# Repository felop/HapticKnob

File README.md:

# Haptic Knob

Développement d’un dispositif à retour haptique contrôlant l’éclairage d’une maquette. Modélisation de textures ressenties sous les doigts, à partir de fonctions simulant des forces de frottement, ressorts internes et effets de seuil, ajustables dynamiquement pour créer crans, irrégularités ou zones fluides. Système conçu autour d’un moteur BLDC et d’un encodeur magnétique (MT6701), piloté par un esp32.

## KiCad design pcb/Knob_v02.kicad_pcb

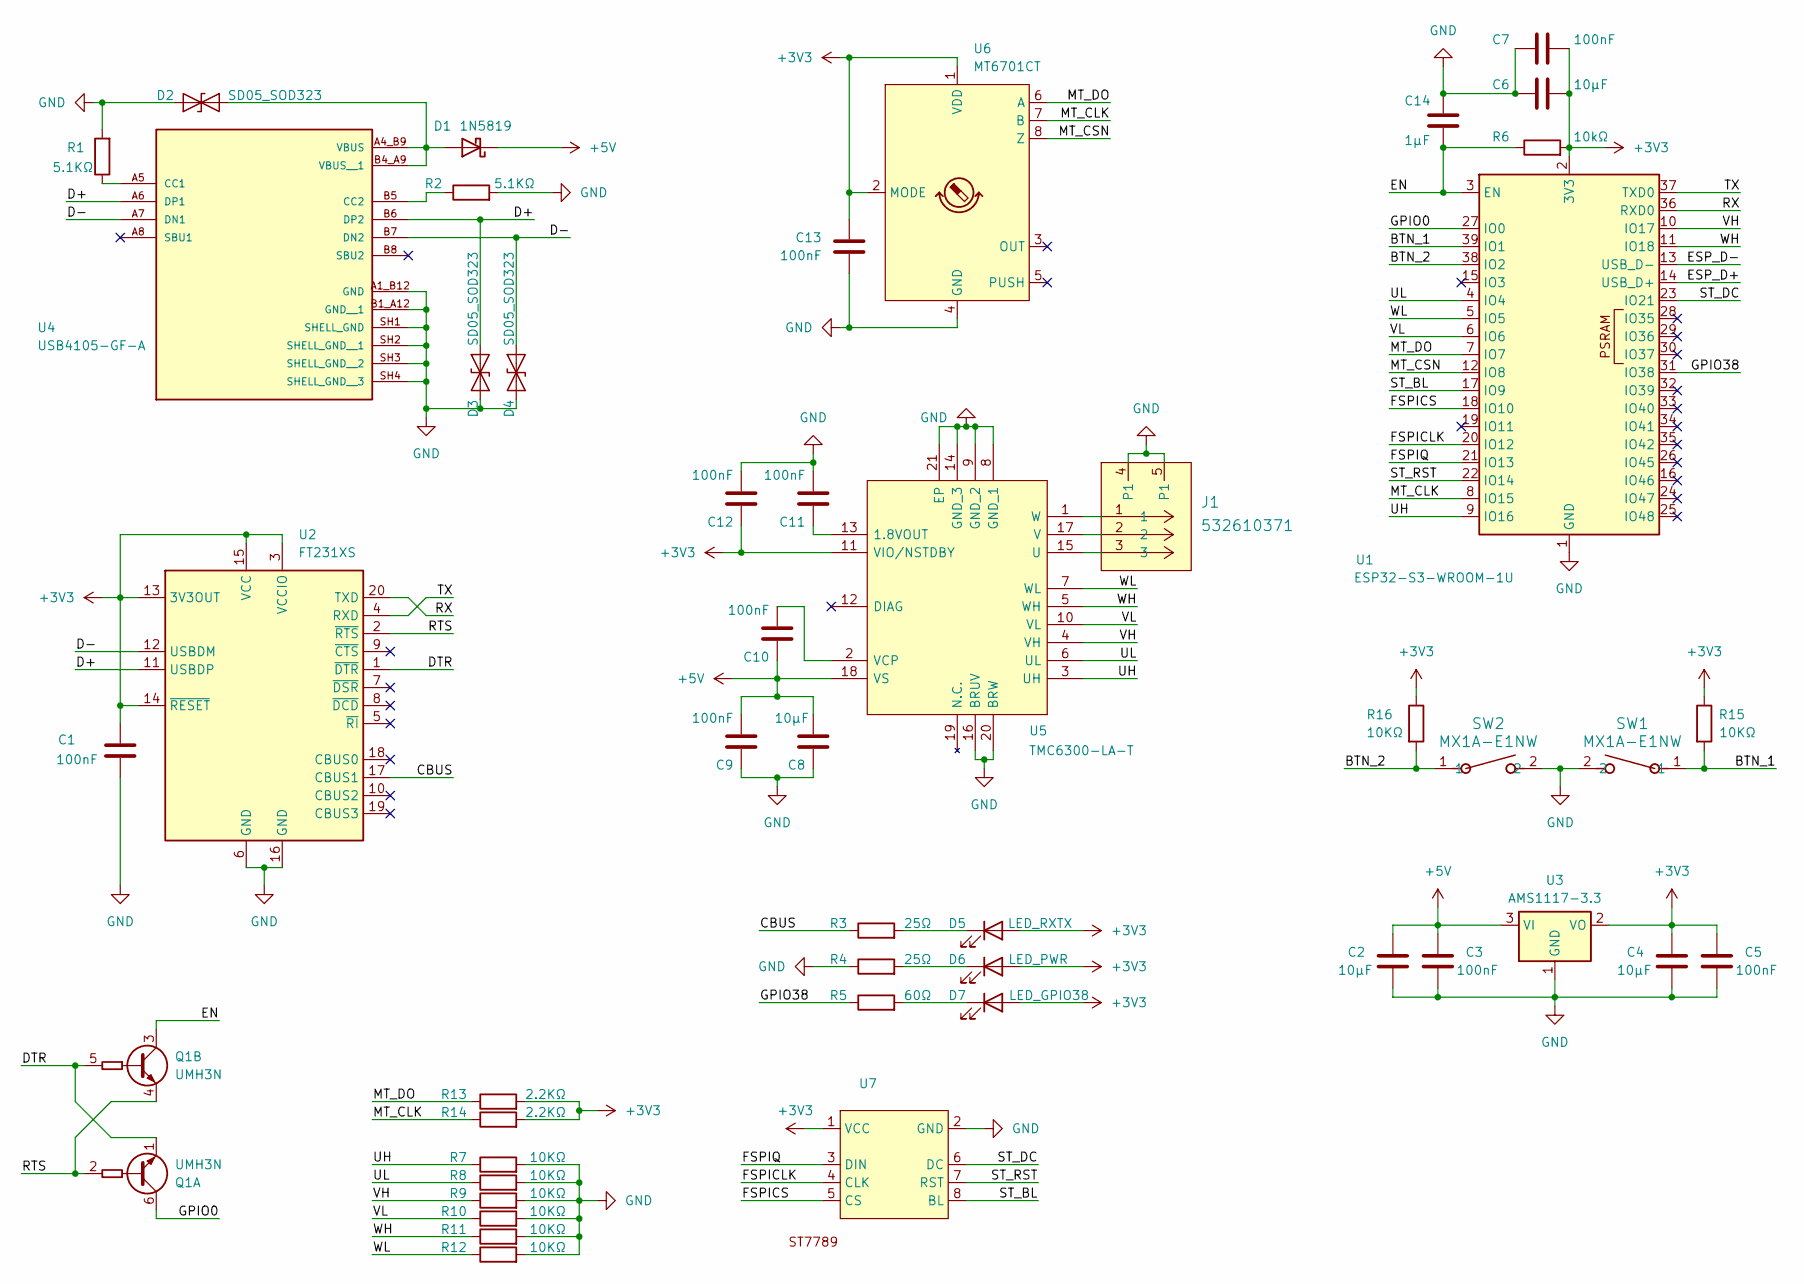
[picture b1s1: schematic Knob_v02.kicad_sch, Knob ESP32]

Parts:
C1, C3, C5, C7, C9, C10, C11, C12, C13: 100nF; C_0603_1608Metric
C2, C4, C6, C8: 10µF; C_0603_1608Metric
C14: 1µF; C_0805_2012Metric
D1: 1N5819; D_SOD-128
D2, D3, D4: SD05_SOD323; D_SOD-323
D5: LED_RXTX; LED_0603_1608Metric
D6: LED_PWR; LED_0603_1608Metric
D7: LED_GPIO38; LED_0805_2012Metric
J1: 532610371; CONN_532610001-SD_03_MOL
Q1: UMH3N; SOT-363_SC-70-6
R1, R2: 5.1KΩ; R_0805_2012Metric
R3, R4: 25Ω; R_0805_2012Metric
R5: 60Ω; R_0805_2012Metric
R6: 10kΩ; R_0603_1608Metric
R7, R8, R9, R10, R11, R12, R15, R16: 10KΩ; R_0603_1608Metric
R13, R14: 2.2KΩ; R_0603_1608Metric
SW1, SW2: MX1A-E1NW; SW_Cherry_MX_1.00u_PCB
U1: ESP32-S3-WROOM-1U
U2: FT231XS; SSOP-20_3.9x8.7mm_P0.635mm
U3: AMS1117-3.3; SOT-223-3_TabPin2
U4: USB4105-GF-A; GCT_USB4105-GF-A; PARTREV B4
U5: TMC6300-LA-T; QFN40P300X300X90-21M; Mouser Part Number 700-TMC6300-LA-T
U6: MT6701CT; SO-8_3.9x4.9mm_P1.27mm
U7: screen

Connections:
+3V3: C1.1, C4.1, C5.1, C6.2, C7.2, C12.1, C13.1, D5.2 (A), D6.2 (A), D7.2 (A), R6.2, R13.2, R14.2, R15.1, R16.1, U1.2 (3V3), U2.3 (VCCIO), U2.13 (3V3OUT), U2.14 (~RESET), U2.15 (VCC), U3.2 (VO), U5.11 (VIO/NSTDBY), U6.1 (VDD), U6.2 (MODE), U7.1 (VCC)
+5V: C2.1, C3.1, C8.2, C9.2, C10.1, D1.1 (K), U3.3 (VI), U5.18 (VS)
/BTN_1: R15.2, SW1.1, U1.39 (IO1)
/BTN_2: R16.2, SW2.1, U1.38 (IO2)
/CBUS: R3.1, U2.17 (CBUS1)
/D+: D3.2 (A2), U2.11 (USBDP), U4.A6 (DP1), U4.B6 (DP2)
/D-: D4.2 (A2), U2.12 (USBDM), U4.A7 (DN1), U4.B7 (DN2)
/DTR: Q1.1 (E1), Q1.5 (B2), U2.1 (~DTR)
/EN: C14.2, Q1.3 (C2), R6.1, U1.3 (EN)
/ESP_D+: U1.14 (USB_D+)
/ESP_D-: U1.13 (USB_D-)
/FSPICLK: U1.20 (IO12), U7.4 (CLK)
/FSPICS: U1.18 (IO10), U7.5 (CS)
/FSPIQ: U1.21 (IO13), U7.3 (DIN)
/GPIO0: Q1.6 (C1), U1.27 (IO0)
/GPIO38: R5.1, U1.31 (IO38)
/MT_CLK: R14.1, U1.8 (IO15), U6.7 (B)
/MT_CSN: U1.12 (IO8), U6.8 (Z)
/MT_DO: R13.1, U1.7 (IO7), U6.6 (A)
/RTS: Q1.2 (B1), Q1.4 (E2), U2.2 (~RTS)
/RX: U1.36 (RXD0), U2.20 (TXD)
/ST_BL: U1.17 (IO9), U7.8 (BL)
/ST_DC: U1.23 (IO21), U7.6 (DC)
/ST_RST: U1.22 (IO14), U7.7 (RST)
/TX: U1.37 (TXD0), U2.4 (RXD)
/UH: R7.1, U1.9 (IO16), U5.3 (UH)
/UL: R8.1, U1.4 (IO4), U5.6 (UL)
/VH: R9.1, U1.10 (IO17), U5.4 (VH)
/VL: R10.1, U1.6 (IO6), U5.10 (VL)
/WH: R11.1, U1.11 (IO18), U5.5 (WH)
/WL: R12.1, U1.5 (IO5), U5.7 (WL)
GND: C1.2, C2.2, C3.2, C4.2, C5.2, C6.1, C7.1, C8.1, C9.1, C11.2, C12.2, C13.2, C14.1, D2.1 (A1), D3.1 (A1), D4.1 (A1), J1.4 (P1), J1.5 (P1), R1.2, R2.2, R4.1, R7.2, R8.2, R9.2, R10.2, R11.2, R12.2, SW1.2, SW2.2, U1.1 (GND), U1.40 (GND), U1.41 (GND), U2.6 (GND), U2.16 (GND), U3.1 (GND), U4.A1_B12 (GND), U4.B1_A12 (GND__1), U4.SH1 (SHELL_GND), U4.SH2 (SHELL_GND__1), U4.SH3 (SHELL_GND__2), U4.SH4 (SHELL_GND__3), U5.8 (GND_1), U5.9 (GND_2), U5.14 (GND_3), U5.16 (BRUV), U5.20 (BRW), U5.21 (EP), U6.4 (GND), U7.2 (GND)
unnamed: D1.2 (A), D2.2 (A2), U4.A4_B9 (VBUS), U4.B4_A9 (VBUS__1)
unnamed: D5.1 (K), R3.2
unnamed: D6.1 (K), R4.2
unnamed: D7.1 (K), R5.2
unnamed: R1.1, U4.A5 (CC1)
unnamed: R2.1, U4.B5 (CC2)
unnamed: C11.1, U5.13 (1.8VOUT)
unnamed: J1.3, U5.15 (U)
unnamed: J1.2, U5.17 (V)
unnamed: C10.2, U5.2 (VCP)
unnamed: J1.1, U5.1 (W)

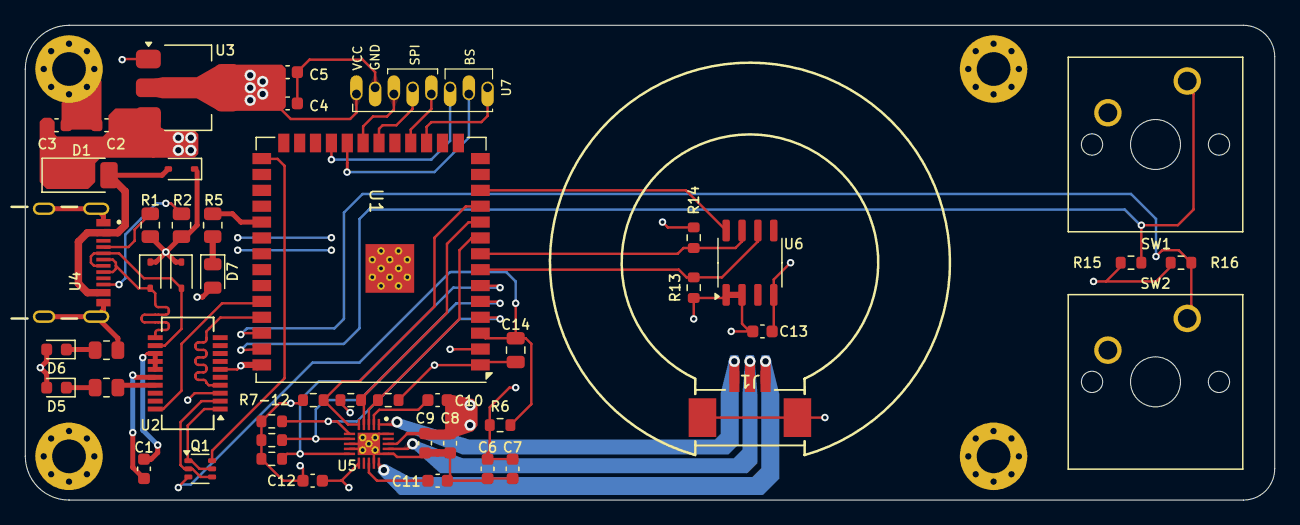
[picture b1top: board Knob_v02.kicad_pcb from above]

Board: 4 copper layers, 100.0 x 38.0 mm, 48 parts (0 on the bottom side), 41 nets.

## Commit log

2026-04-15 added pcb files
2026-05-07 added README.md
